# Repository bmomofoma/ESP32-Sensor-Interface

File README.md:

# ESP32-S3 Sensor Hub

I built this board because I wanted a compact, reliable hardware platform that could pull data from five different sensors at the same time without turning the signal lines into a noisy mess. It’s a 4-layer board centered around an ESP32-S3 that acts as a central data hub, ideal for robotics or autonomous systems. 

---

## Why I Made These Design Choices

### Moving to a 4-Layer Board
A lot of simple projects stick to 2 layers, but running high-frequency data lines right next to power traces is a recipe for a noisy bus. 
* I made **Layer 2 a solid Ground plane** to give all the signals a tight, clean return path, which knocks down cross-talk immensely.
* **Layer 3 is a power plane**, which lets me cleanly route the 3.3V regulated line without running into routing bottlenecks.

### Powering the Array Safely
The board takes 5V from a USB-C port and drops it to 3.3V using an `AP7361C-33E` linear regulator. 
* The ESP32-S3 spikes in current when its Wi-Fi or Bluetooth radios kick on. This regulator can handle up to 1A, keeping the rail steady so the sensors don't glitch.
* For debugging safety, I put a ferrite bead, a Schottky diode, and a resettable polyfuse on the input to protect the expensive components downstream if I accidentally short something on the bench.

### Choosing Flat Pads (ENIG) over HASL
Two of the sensors—the `BMI088` IMU and the `MMC5633NJL` magnetometer—come in fine-pitch LGA and QFN packages, meaning the pins are tiny and sit entirely underneath the chip. 
* Standard HASL board finishes leave uneven mounds of solder on the pads, which causes these tiny chips to float or bridge during soldering. 
* I specified an **ENIG (Gold) finish** for manufacturing because it guarantees perfectly flat pads, making reflow much easier.

---

## The Hardware Setup

All five sensors communicate over a single shared $\text{I}^2\text{C}$ bus using **GPIO8 (SDA)** and **GPIO9 (SCL)**, pulled up by $4.7\text{ k}\Omega$ resistors.

| Sensor | Part Number | What It Measures |
| :--- | :--- | :--- |
| **IMU (6-Axis)** | BMI088 | Pitch, roll, yaw, and high-G acceleration |
| **Magnetometer** | MMC5633NJL | Compass heading orientation |
| **Pressure/Altimeter** | BMP280 | Altitude & atmospheric pressure |
| **Temp/Humidity** | SHT4x | Local environmental data |
| **Time-of-Flight (ToF)** | VL53L0X | Precision optical distance for proximity |

> 🛠️ **Hardware Note:** The VL53L0X distance sensor hardcodes itself to address `0x29` on boot, which can cause bus issues. To fix this, I routed its hardware shutdown pin (**XSHUT**) to **GPIO48** so the firmware can hard-reset the chip and dynamically change its address if needed.

---

## Layout Constraints & Debugging

* **Antenna Keep-Out:** There is a strict, cross-hatched keep-out zone on all layers around the ESP32’s PCB antenna. No copper, traces, or mounting screws can go near it, keeping the wireless signal strong.
* **Lab Debugging Headers:** I exposed the $\text{I}^2\text{C}$ lines on header **J2** and the main serial UART lines on header **J3**. This makes it easy to clip on a logic analyzer or hook up a USB-to-UART bridge to watch terminal logs while writing firmware.
* **Buttons & LEDs:** Included a reset button, a boot button, a green power LED, and a red status LED mapped to **GPIO3** for basic visual debugging.

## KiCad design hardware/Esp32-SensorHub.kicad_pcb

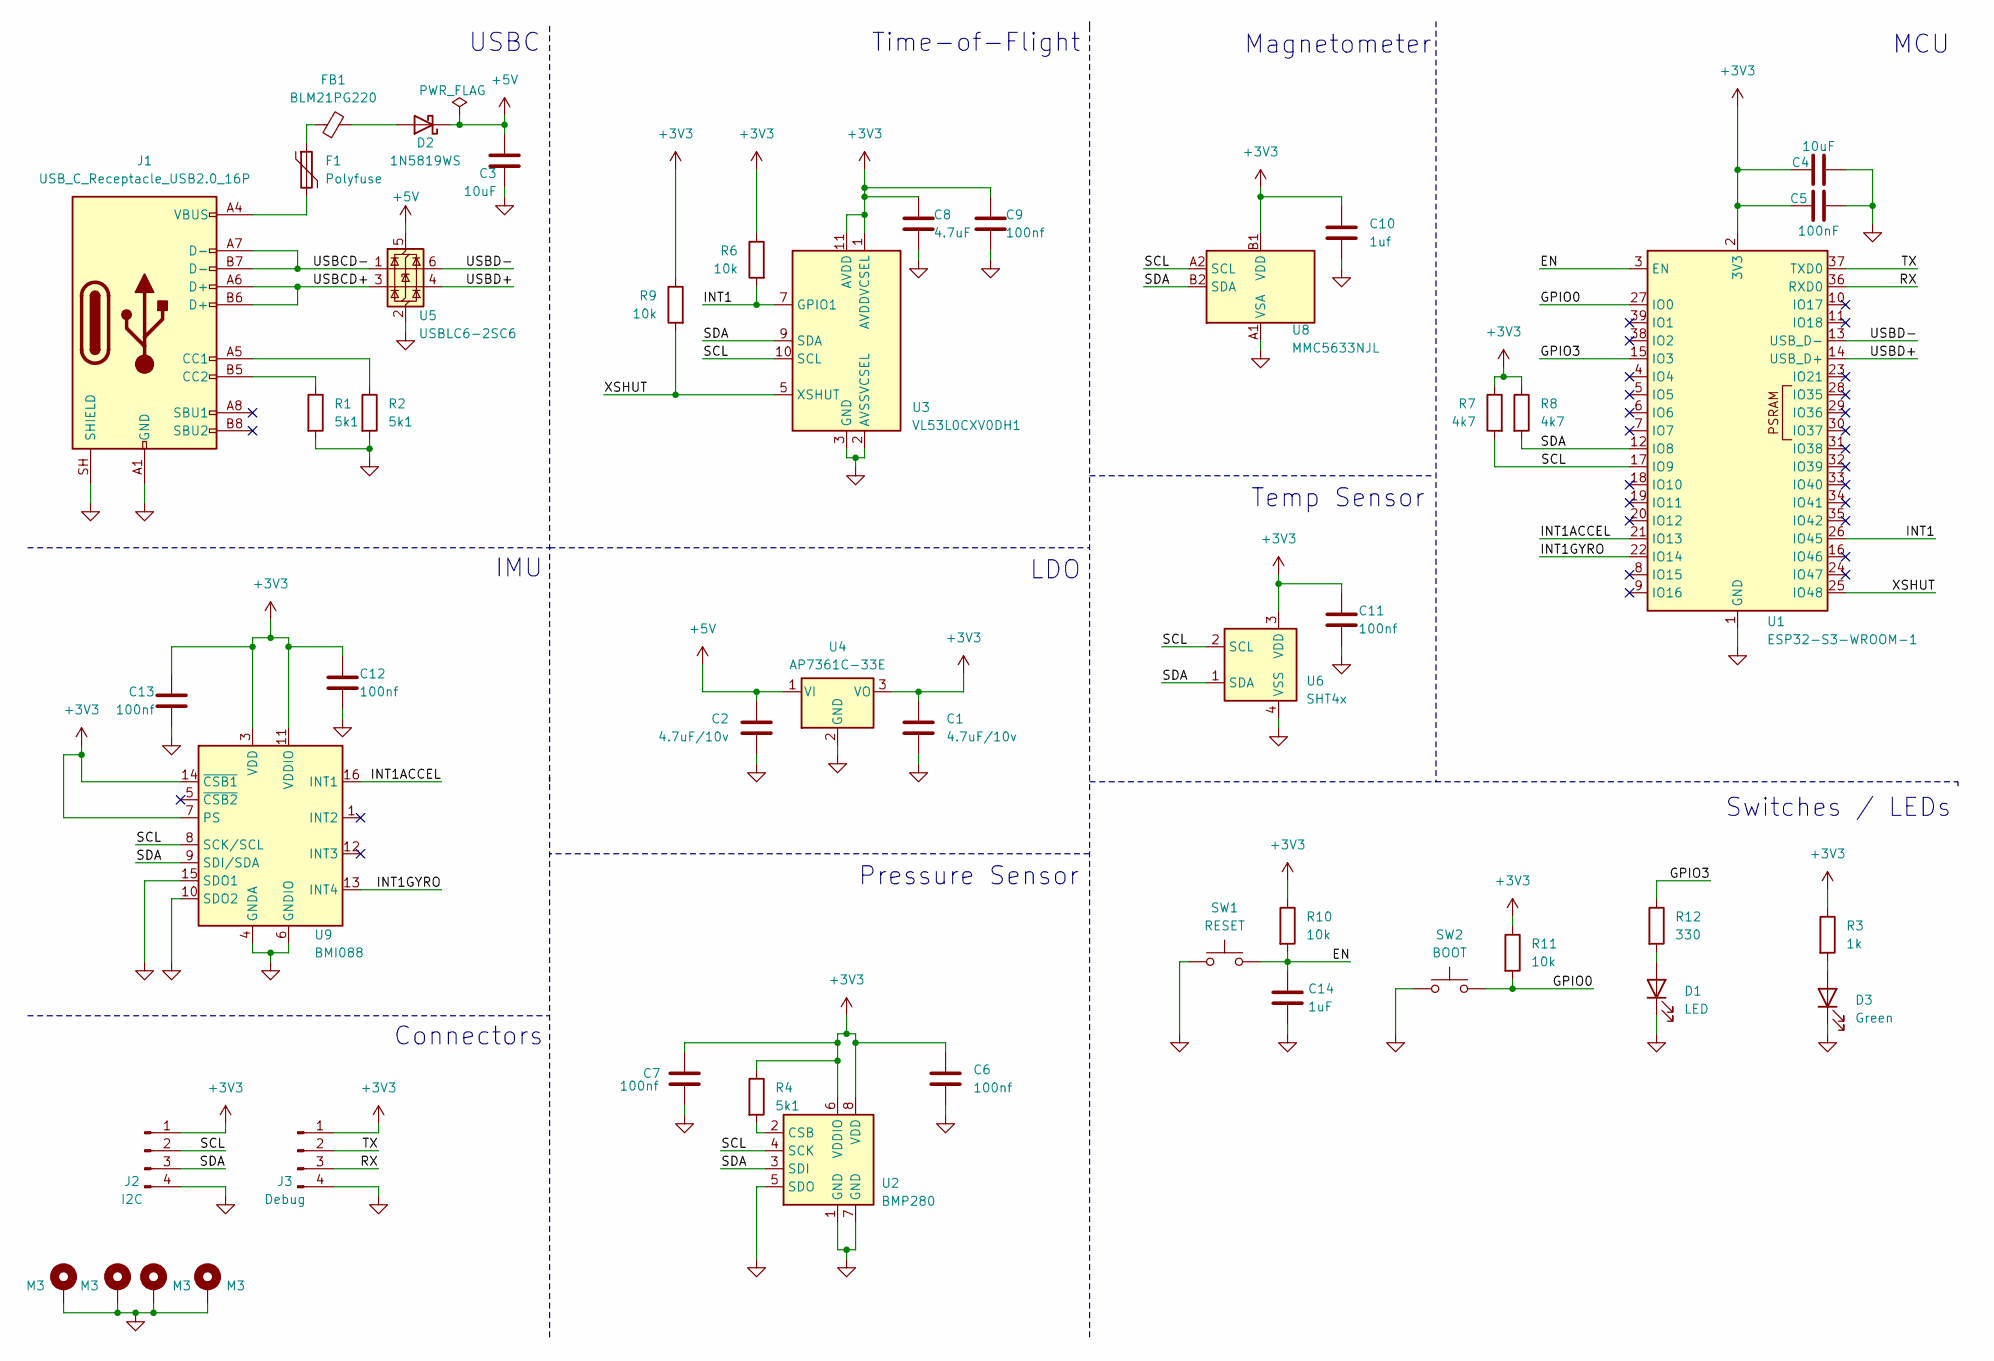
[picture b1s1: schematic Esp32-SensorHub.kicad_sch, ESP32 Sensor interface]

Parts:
C1, C2: 4.7uF/10v; C_0805_2012Metric
C3, C4: 10uF; C_0805_2012Metric
C5: 100nF; C_0603_1608Metric
C6, C7, C9, C11, C12, C13: 100nf; C_0603_1608Metric
C8: 4.7uF; C_0603_1608Metric
C10: 1uf; C_0603_1608Metric
C14: 1uF; C_0603_1608Metric
D1: LED; LED_0603_1608Metric
D2: 1N5819WS; D_SOD-323
D3: Green; LED_0603_1608Metric
F1: Polyfuse; Fuse_0805_2012Metric
FB1: BLM21PG220; L_0805_2012Metric
H1, H2, H3, H4: M3; MountingHole_3.2mm_M3_Pad_Via
J1: USB_C_Receptacle_USB2.0_16P; USB_C_Receptacle_GCT_USB4105-xx-A_16P_TopMnt_Horizontal
J2: I2C; PinHeader_1x04_P2.54mm_Vertical
J3: Debug; PinHeader_1x04_P2.54mm_Vertical
R1, R2, R4: 5k1; R_0603_1608Metric
R3: 1k; R_0603_1608Metric
R6, R9, R10, R11: 10k; R_0603_1608Metric
R7, R8: 4k7; R_0603_1608Metric
R12: 330; R_0603_1608Metric
SW1: RESET; SW_SPST_PTS810
SW2: BOOT; SW_SPST_PTS810
U1: ESP32-S3-WROOM-1
U2: BMP280; Bosch_LGA-8_2x2.5mm_P0.65mm_ClockwisePinNumbering
U3: VL53L0CXV0DH1; ST_VL53L1x
U4: AP7361C-33E; SOT-223-3_TabPin2
U5: USBLC6-2SC6; SOT-23-6
U6: SHT4x; Sensirion_DFN-4_1.5x1.5mm_P0.8mm_SHT4x_NoCentralPad
U8: MMC5633NJL; WLP-4_0.86x0.86mm_P0.4mm
U9: BMI088; Bosch_LGA-16_4.5x3mm_P0.5mm_LayoutBorder7x1y_ClockwisePinNu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

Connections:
+3V3: C1.1, C4.1, C5.1, C6.1, C7.1, C8.1, C9.1, C10.1, C11.1, C12.1, C13.1, J2.1, J3.1, R3.1, R4.1, R6.1, R7.1, R8.1, R9.1, R10.1, R11.1, U1.2 (3V3), U2.6 (VDDIO), U2.8 (VDD), U3.1 (AVDDVCSEL), U3.11 (AVDD), U4.3 (VO), U6.3 (VDD), U8.B1 (VDD), U9.3 (VDD), U9.7 (PS), U9.11 (VDDIO), U9.14 (~CSB1)
+5V: C2.1, C3.1, D2.1 (K), U4.1 (VI), U5.5 (VBUS)
/EN: C14.2, R10.2, SW1.2, U1.3 (EN); also elsewhere on the board
/GPIO0: R11.2, SW2.2, U1.27 (IO0); also elsewhere on the board
/GPIO3: R12.1, U1.15 (IO3)
/INT1: R6.2, U1.26 (IO45), U3.7 (GPIO1)
/INT1ACCEL: U1.21 (IO13), U9.16 (INT1)
/INT1GYRO: U1.22 (IO14), U9.13 (INT4)
/RX: J3.3, U1.36 (RXD0)
/SCL: J2.2, R7.2, U1.17 (IO9), U2.4 (SCK), U3.10 (SCL), U6.2 (SCL), U8.A2 (SCL), U9.8 (SCK/SCL)
/SDA: J2.3, R8.2, U1.12 (IO8), U2.3 (SDI), U3.9 (SDA), U6.1 (SDA), U8.B2 (SDA), U9.9 (SDI/SDA)
/TX: J3.2, U1.37 (TXD0)
/USBCD+: J1.A6 (D+), J1.B6 (D+), U5.3 (I/O2)
/USBCD-: J1.A7 (D-), J1.B7 (D-), U5.1 (I/O1)
/USBD+: U1.14 (USB_D+), U5.4 (I/O2)
/USBD-: U1.13 (USB_D-), U5.6 (I/O1)
/XSHUT: R9.2, U1.25 (IO48), U3.5 (XSHUT)
GND: C1.2, C2.2, C3.2, C4.2, C5.2, C6.2, C7.2, C8.2, C9.2, C10.2, C11.2, C12.2, C13.2, C14.1, D1.1 (K), D3.1 (K), H1.1 (1_1), H2.1 (1_1), H3.1 (1_1), H4.1 (1_1), J1.A1 (GND), J1.A12 (GND), J1.B1 (GND), J1.B12 (GND), J1.SH (SHIELD), J2.4, J3.4, R1.2, R2.2, SW1.1, SW2.1, U1.1 (GND), U1.40 (GND), U1.41 (GND), U2.1 (GND), U2.5 (SDO), U2.7 (GND), U3.2 (AVSSVCSEL), U3.3 (GND), U3.4 (GND), U3.6 (GND), U3.12 (GND), U4.2 (GND), U5.2 (GND), U6.4 (VSS), U8.A1 (VSA), U9.2 (GNDA), U9.4 (GNDA), U9.6 (GNDIO), U9.10 (SDO2), U9.15 (SDO1); also elsewhere on the board
unnamed: D1.2 (A), R12.2
unnamed: D2.2 (A), FB1.2
unnamed: D3.2 (A), R3.2
unnamed: F1.1, FB1.1
unnamed: F1.2, J1.A4 (VBUS), J1.A9 (VBUS), J1.B4 (VBUS), J1.B9 (VBUS)
unnamed: J1.A5 (CC1), R2.1
unnamed: J1.B5 (CC2), R1.1
unnamed: R4.2, U2.2 (CSB)

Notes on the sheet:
Magnetometer
Pressure Sensor
USBC
Connectors
LDO
IMU
Temp Sensor
Switches / LEDs
Time-of-Flight
MCU

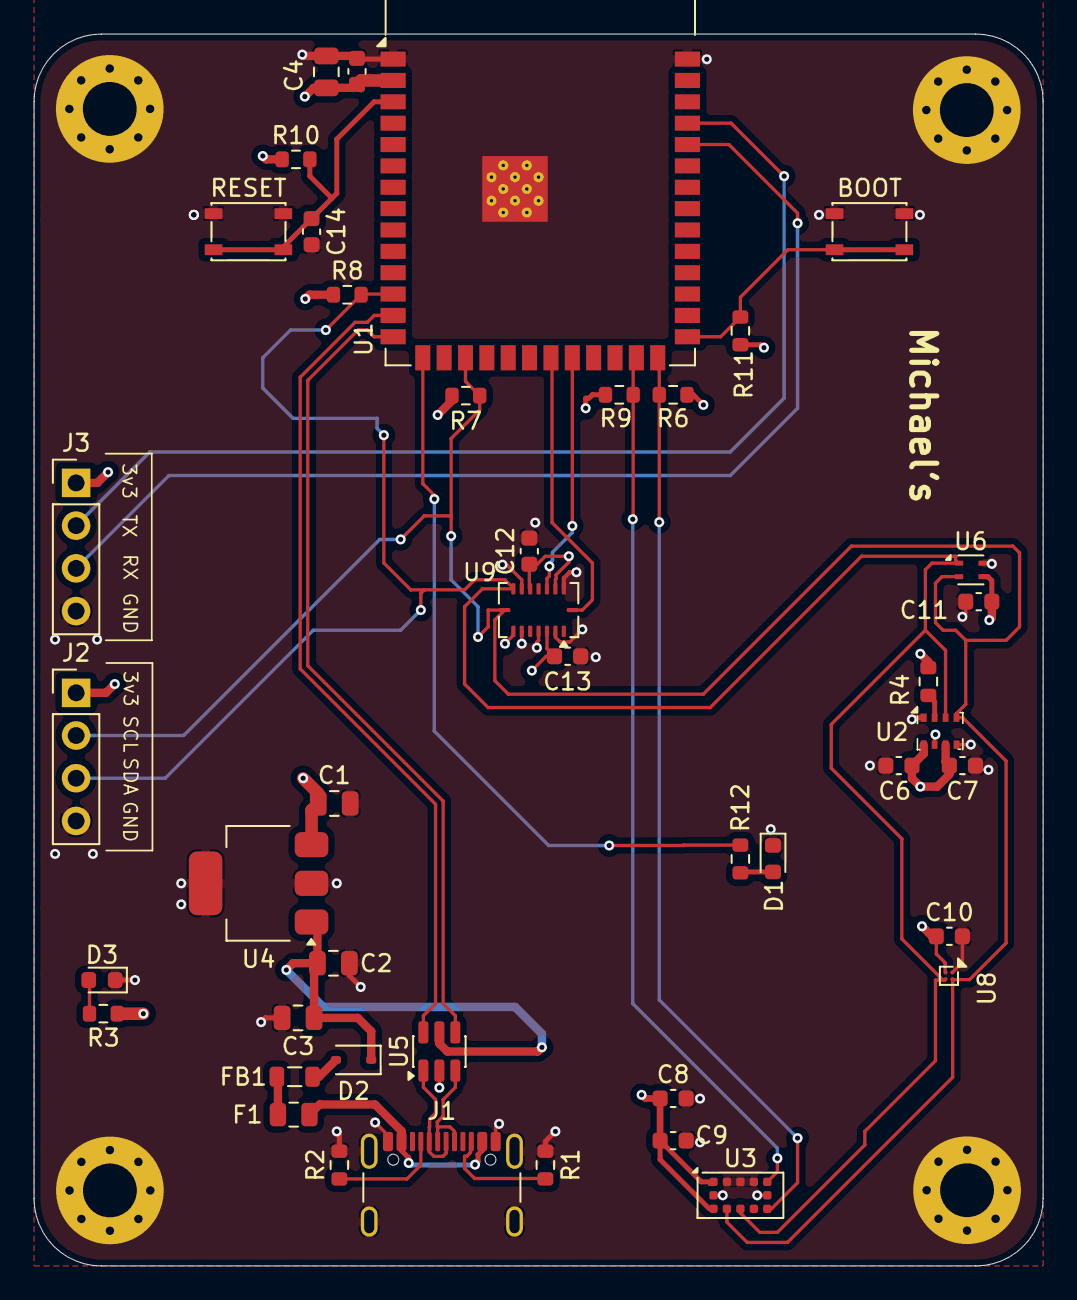
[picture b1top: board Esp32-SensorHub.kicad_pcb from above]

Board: 4 copper layers, 60.0 x 73.2 mm, 47 parts (0 on the bottom side), 26 nets.

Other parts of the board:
BOOT: BOOT; SW_SPST_PTS810
RESET: RESET; SW_SPST_PTS810

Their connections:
/EN: RESET.2; also elsewhere on the board
/GPIO0: BOOT.2; also elsewhere on the board
GND: BOOT.1, RESET.1; also elsewhere on the board

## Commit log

2026-06-08 Update README.md
    Added project description
2026-06-08 Update README.md
    Updated Description
2026-06-08 Create placeholder
